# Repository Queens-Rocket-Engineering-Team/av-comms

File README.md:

# Avionics Telemetry (Communications Module, Ground Station, Live Camera etc)
> 2023-2025 Season - Telemetry Projects

-  Repo contains board's **firmware**, **schematics**, and related **documentation and datasheets**.
-  The **Main** branch contains current functional hardware/software
-  **Branches** contain board revisions/versions or planned features/fixes.
-  If you're contributing, **make sure you're working in a branch other than Main**

### Folder Structure
- [`/Schematics`](./Schematics/) : PCB design files (KiCad V8)  
- [`/Firmware`](./Firmware/) : Arduino C/C++ code (for STM32)
- [`/Datasheets`](./Datasheets/) : Datasheets and reference materials

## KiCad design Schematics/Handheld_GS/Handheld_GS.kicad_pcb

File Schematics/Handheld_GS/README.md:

# Portable Ground Station

This directory contains the V1.2 revision of the ground station. It no longer has iss several known problems;

### Updates
- Removed I2C ADC, switched to ESP32-ADCs
- Using direct USB+/- for programming, removed uart bridge
- Added V_BCKP for GPS, (copied circuit from gps antenna board)

### Future Suggestions
- Look into using the MAX17043 for battery management
- Look into using TP4056 for battery charging (cheaper)
- switch to a new battery switch cause it breaks

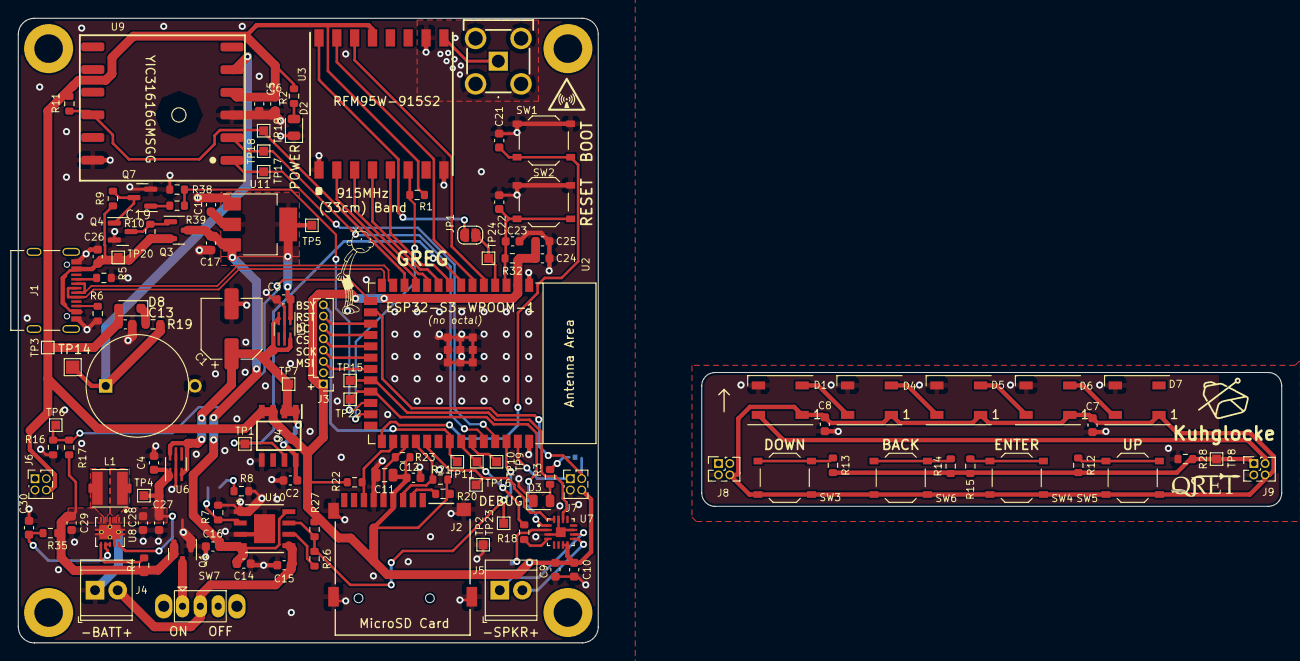
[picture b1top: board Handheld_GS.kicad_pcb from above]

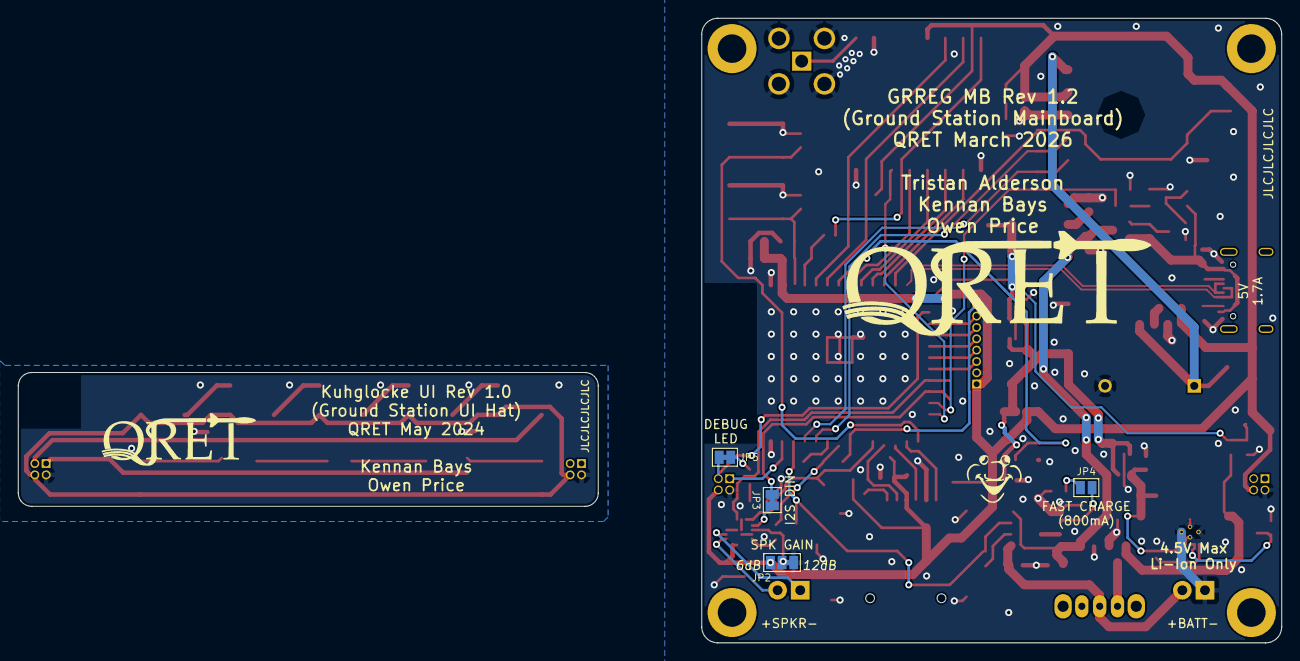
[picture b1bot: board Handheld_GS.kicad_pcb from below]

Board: 2 copper layers, 65.0 x 70.0 mm, 129 parts (4 on the bottom side), 82 nets.

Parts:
AE1: Antenna; PCB114SMAFRAJA
C1: 100uF; CP_Elec_6.3x5.9
C2, C5, C9, C12, C16, C21, C22, C25, C30: 0.1uF; C_0603_1608Metric
C3, C4, C7, C8, C13, C14, C15, C23: 1uF; C_0603_1608Metric
C6: 4.7uF; C_0603_1608Metric
C10, C17, C18, C24, C26, C27, C28, C29: 10uF; C_0603_1608Metric
C11: 47uF; C_0805_2012Metric
C19: 330mF; CB5R5334HF-ZJP
D1, D4, D5, D6, D7: WS2812B; LED_WS2812B_PLCC4_5.0x5.0mm_P3.2mm
D2: INT_PWR_LED (RED); LED_0805_2012Metric
D3: DB_LED (GRN); LED_0805_2012Metric
D8: 1N5819WS; D_SOD-323_HandSoldering
H1, H2, H3, H4: MountingHole; MountingHole_3.2mm_M3_ISO14580_Pad
J1: USB_C_Female_USB2_Small; USB_C_DB-108PWB
J2: MSD-1-A MicroSD Slot; MicroSD_MSD-1-A
J3: PinHeader_1x08_P1.27mm_Vertical
J4: 1S Li-Ion Cell; TerminalBlock_TE_282834-2_1x02_P2.54mm_Horizontal
J5: Speaker; TerminalBlock_TE_282834-2_1x02_P2.54mm_Horizontal
J6: MB_A; PinSocket_2x02_P1.27mm_Vertical
J7: MB_B; PinSocket_2x02_P1.27mm_Vertical
J8: DB_A; HPH2-A-04-UA_PINS
J9: DB_B; HPH2-A-04-UA_PINS
JP1: DIO2_EN; SolderJumper-2_P1.3mm_Open_RoundedPad1.0x1.5mm
JP2: Gain; SolderJumper-3_P1.3mm_Bridged12_Pad1.0x1.5mm_NumberLabels
JP3: SPK_DIN; SolderJumper-2_P1.3mm_Bridged_Pad1.0x1.5mm
JP4: FastCharge; SolderJumper-2_P1.3mm_Open_Pad1.0x1.5mm
JP5: DB_LED_EN; SolderJumper-2_P1.3mm_Bridged_Pad1.0x1.5mm
L1: 2.2uH; L_Taiyo-Yuden_MD-4040
Q1, Q3: AO3401A; SOT-23
Q4, Q7: AO3400A; SOT-23
R1, R3, R11, R16, R20, R21, R22, R23, R26, R27, R32: 10k; R_0603_1608Metric
R2: 1.8k; R_0603_1608Metric
R4, R9, R18, R38: 100k; R_0603_1608Metric
R5, R6: 5.1k; R_0603_1608Metric
R7: 2.4k; R_0603_1608Metric
R8: 3.9k; R_0603_1608Metric
R10: 51k; R_0603_1608Metric
R12, R39: 510; R_0603_1608Metric
R13, R28: 1k; R_0603_1608Metric
R14: 2k; R_0603_1608Metric
R15: 5.6k; R_0603_1608Metric
R17: 20k; R_0603_1608Metric
R19: 100R; R_0603_1608Metric
R35: 100; R_0603_1608Metric
SW1: SW_ESP_BOOT_MODE; SW_Push_1P1T_XKB_TS-1187A
SW2: SW_ESP_RESET; SW_Push_1P1T_XKB_TS-1187A
SW3: SW_DOWN; SW_Push_1P1T_XKB_TS-1187A
SW4: SW_ENTER; SW_Push_1P1T_XKB_TS-1187A
SW5: SW_UP; SW_Push_1P1T_XKB_TS-1187A
SW6: SW_BACK; SW_Push_1P1T_XKB_TS-1187A
SW7: PWR; SS-12D07-VG 4 NS GA PA
TP1: TP_ISENSE; TestPoint_Pad_1.0x1.0mm
TP2: TP_GND; TestPoint_Pad_1.0x1.0mm
TP3: TP_3V3; TestPoint_Pad_1.0x1.0mm
TP4: TP_VPSU; TestPoint_Pad_1.0x1.0mm
TP5: TP_VUSB; TestPoint_Pad_1.0x1.0mm
TP6: B_SENSE; TestPoint_Pad_1.0x1.0mm
TP7: TP_MUX; TestPoint_Pad_1.0x1.0mm
TP8: TP_BTN; TestPoint_Pad_1.0x1.0mm
TP9: IO42; TestPoint_Pad_1.0x1.0mm
TP10: IO41; TestPoint_Pad_1.0x1.0mm
TP11: IO40; TestPoint_Pad_1.0x1.0mm
TP14: BKP; TestPoint_Pad_1.5x1.5mm
TP15: I2S_LRCLK; TestPoint_Pad_1.0x1.0mm
TP16: I2S_BLCK; TestPoint_Pad_1.0x1.0mm
TP17: GPS_RX; TestPoint_Pad_1.0x1.0mm
TP18: GPS_TX; TestPoint_Pad_1.0x1.0mm
TP19: GPS_RST; TestPoint_Pad_1.0x1.0mm
TP20: 5V_RAW; TestPoint_Pad_1.0x1.0mm
TP22: I2S_DIN; TestPoint_Pad_1.0x1.0mm
TP23: CHRG_STAT; TestPoint_Pad_1.0x1.0mm
TP24: IO4; TestPoint_Pad_1.0x1.0mm
U2: ESP32-S3-WROOM-1
U3: RFM95W-915S2; RFM95W
U4: ACS70331EOLC; SOIC127P600X175-8N
U5, U6: LM66100DCKR; SC-70-6_Handsoldering
U7: MAX98357AETE_T; MAX98357_QFN50P300X300X80-17N
U8: TPS63001DRCR; Texas_DRC0010J_ThermalVias
U9: YIC31616GMSGG GPS; YIC31616GMSGG
U10: TPB4056B2X-ES1R; ES1ESOP-8-F_TPK
U11: AMS1117-3.3; SOT-223-3_TabPin2

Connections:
5V_OFF: R38.1, R39.1, U2.24 (GPIO47/SPICLK_P/SUBSPICLK_P_DIFF)
5V_RAW: C26.2, J1.A4 (VBUS), J1.A9 (VBUS), J1.B4 (VBUS), J1.B9 (VBUS), Q3.2 (S), R9.1, R10.1, TP20.1
+3.3V: C5.2, C6.2, C9.1, C10.1, C11.1, C12.1, C13.1, C24.1, C25.1, D8.2 (A), J2.4 (VDD), J3.1 (VCC), J6.4, J7.4, JP2.3 (B), R1.2, R2.2, R11.1, R20.1, R21.1, R22.1, R23.1, R27.2, R32.1, TP3.1, U2.2 (3V3), U3.13 (3.3V), U4.3 (IP-), U4.4 (IP-), U7.7 (VDD), U7.8 (VDD__1), U9.4 (VCC)
+3.3VA: C7.2, C8.2, D1.1 (VDD), D4.1 (VDD), D5.1 (VDD), D6.1 (VDD), D7.1 (VDD), J8.4, J9.4, SW3.1, SW4.1, SW5.1, SW6.1
+5V: C14.1, C16.2, C17.1, Q3.3 (D), U10.4 (VIN), U10.8 (CE), U11.3 (VI)
+BATT: C29.1, Q1.2 (S), R4.1, R17.1, R35.1, U8.5 (VIN)
/GPS_BCKP: C19.1, R19.2, TP14.1, U9.5 (V_BCKP)
/LA: L1.2, U8.2 (L2)
/LB: L1.1, U8.4 (L1)
ARGB_DATA: J7.3, JP5.1 (A), U2.16 (GPIO46)
ARGB_DATA_DB: D1.4 (DIN), J9.3
BATT_SENSE: R16.1, R17.2, TP6.1, U2.15 (GPIO3/TOUCH3/ADC1_CH2)
BUTTONS: J7.1, U2.39 (GPIO1/TOUCH1/ADC1_CH0)
BUTTONS_DB: J9.1, R12.2, R13.2, R14.1, R15.2, R28.2, TP8.1
CHRG_STAT: R26.2, R27.1, TP23.1, U2.38 (GPIO2/TOUCH2/ADC1_CH1), U10.7 (CHRG)
CLK_SDMMC: J2.5 (CLK), R23.2, U2.29 (SPIIO7/GPIO36/FSPICLK/SUBSPICLK)
CMD_SDMMC: J2.3 (CMD), R21.2, U2.30 (SPIDQS/GPIO37/FSPIQ/SUBSPIQ)
CS_EINK: J3.5 (CS), U2.19 (GPIO11/TOUCH11/ADC2_CH0/FSPID/FSPIIO5/S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)
CS_RF: U2.8 (GPIO15/U0RTS/ADC2_CH4/XTAL_32K_P), U3.5 (NSS)
CURR_SENSE: TP1.1, U2.7 (GPIO7/TOUCH7/ADC1_CH6), U4.7 (VOUT)
D0_SDMMC: J2.7 (DAT0), R22.2, U2.28 (SPIIO6/GPIO35/FSPID/SUBSPID)
DIO0_RF: U2.5 (GPIO5/TOUCH5/ADC1_CH4), U3.14 (DIO0)
DIO1_RF: U2.6 (GPIO6/TOUCH6/ADC1_CH5), U3.15 (DIO1)
DIO2_RF: JP1.2 (B), TP24.1, U2.4 (GPIO4/TOUCH4/ADC1_CH3)
EINK_BUSY: J3.8 (BUSY), TP11.1, U2.33 (MTDO/GPIO40/CLK_OUT2)
EINK_DC: J3.6 (DC), U2.18 (GPIO10/TOUCH10/ADC1_CH9/FSPICS0/FSPIIO4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)
ESP32_EN: C22.2, C23.2, R32.2, SW2.2, U2.3 (EN)
GND: AE1.2 (Shield), C1.2, C2.2, C3.2, C4.2, C5.1, C6.1, C9.2, C10.2, C11.2, C12.2, C13.2, C14.2, C15.1, C16.1, C17.2, C18.2, C19.2, C21.1, C22.1, C23.1, C24.2, C25.2, C26.1, C27.2, C28.2, C29.2, C30.2, D2.1 (K), D3.1 (K), J1.A1 (GND), J1.A12 (GND), J1.B1 (GND), J1.B12 (GND), J2.6 (VSS), J2.10 (SHIELD), J3.2 (GND), J4.1, J6.2, J7.2, JP2.1 (A), Q1.1 (G), Q4.2 (S), Q7.2 (S), R5.2, R6.2, R7.1, R8.2, R16.2, R38.2, SW1.1, SW2.1, TP2.1, U2.1 (GND), U2.40 (GND), U2.41 (GND), U3.1 (GND), U3.8 (GND), U3.10 (GND), U4.5 (GND), U5.2 (GND), U5.5 (ST), U6.2 (GND), U6.5 (ST), U7.3 (GND), U7.11 (GND__1), U7.15 (GND__2), U7.17 (EP), U8.3 (PGND), U8.9 (GND), U8.11 (PGND), U9.3 (GND), U9.12 (GND), U10.1 (TEMP), U10.3 (GND), U10.9 (GND), U11.1 (GND)
GND2: C7.1, C8.1, D1.3 (VSS), D4.3 (VSS), D5.3 (VSS), D6.3 (VSS), D7.3 (VSS), J8.2, J9.2, R28.1
GPIO0: C21.2, SW1.2, U2.27 (GPIO0/BOOT)
GPS_RST: R11.2, TP19.1, U2.12 (GPIO8/TOUCH8/ADC1_CH7/SUBSPICS1), U9.10 (RESET)
I2S_BCLK_SPK: TP16.1, U2.31 (GPIO38/FSPIWP/SUBSPIWP), U7.16 (BCLK)
I2S_DIN_SPK: JP3.2 (B), TP22.1, U2.23 (GPIO21)
I2S_LRCLK_SPK: TP15.1, U2.22 (GPIO14/TOUCH14/ADC2_CH3/FSPIWP/FSPIDQS/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), U7.14 (LRCLK)
MISO_EINK: TP9.1, U2.35 (MTMS/GPIO42)
MISO_RF: U2.11 (GPIO18/U1RXD/ADC2_CH7/CLK_OUT3), U3.2 (MISO)
MOSI_EINK: J3.3 (DIN), U2.21 (GPIO13/TOUCH13/ADC2_CH2/FSPIQ/FSPIIO7/S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)
MOSI_RF: U2.10 (GPIO17/U1TXD/ADC2_CH6), U3.3 (MOSI)
unnamed: AE1.1 (A), U3.9 (ANT)
unnamed: D1.2 (DOUT), D4.4 (DIN)
unnamed: D2.2 (A), R2.1
unnamed: D3.2 (A), R3.1
unnamed: D4.2 (DOUT), D5.4 (DIN)
unnamed: D5.2 (DOUT), D6.4 (DIN)
unnamed: D6.2 (DOUT), D7.4 (DIN)
unnamed: D8.1 (K), R19.1
unnamed: J1.A5 (CC1), R5.1
unnamed: J1.B5 (CC2), R6.1
unnamed: J2.2 (DAT3/CD), R20.2
unnamed: J5.1, U7.10 (OUTN)
unnamed: J5.2, U7.9 (OUTP)
unnamed: JP1.1 (A), U3.16 (DIO2)
unnamed: JP2.2 (C), U7.2 (GAIN_SLOT)
unnamed: JP3.1 (A), U7.1 (DIN)
unnamed: JP4.1 (A), R8.1
unnamed: JP4.2 (B), R7.2, U10.2 (PROG)
unnamed: JP5.2 (B), R3.2
unnamed: Q1.3 (D), SW7.1 (A)
unnamed: Q3.1 (G), Q4.3 (D), R10.2
unnamed: Q4.1 (G), Q7.3 (D), R9.2
unnamed: Q7.1 (G), R39.2
unnamed: R12.1, SW5.2
unnamed: R13.1, SW3.2
unnamed: R14.2, SW6.2
unnamed: R15.1, SW4.2
unnamed: R18.2, U7.4 (SD_MODE)
unnamed: R4.2, U8.6 (EN)
unnamed: C30.1, R35.2, U8.7 (PS/SYNC), U8.8 (VINA)
unnamed: R26.1, U10.6 (STBY)
RAW_BATT: C15.2, J4.2, SW7.2 (B), U10.5 (BAT)
RESET_EINK: J3.7 (RST), U2.17 (GPIO9/TOUCH9/ADC1_CH8/FSPIHD/SUBSPIHD)
RESET_RF: R1.1, U2.25 (GPIO48/SPICLK_N/SUBSPICLK_N_DIFF), U3.6 (RESET)
SCK_EINK: J3.4 (CLK), U2.20 (GPIO12/TOUCH12/ADC2_CH1/FSPICLK/FSPIIO6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)
SCK_RF: U2.9 (GPIO16/U0CTS/ADC2_CH5/XTAL_32K_N), U3.4 (SCK)
SPK_ON: R18.1, TP10.1, U2.34 (MTDI/GPIO41/CLK_OUT1)
UART1_GPS_RX: TP18.1, U2.36 (U0RXD/GPIO44/CLK_OUT2), U9.2 (TXD)
UART1_GPS_TX: TP17.1, U2.37 (U0TXD/GPIO43/CLK_OUT1), U9.1 (RXD)
USB_D+: J1.A6 (D+), J1.B6 (D+), U2.14 (GPIO20/U1CTS/ADC2_CH9/CLK_OUT1/USB_D+)
USB_D-: J1.A7 (D-), J1.B7 (D-), U2.13 (GPIO19/U1RTS/ADC2_CH8/CLK_OUT2/USB_D-)
V_MUX: C1.1, C2.1, TP7.1, U4.1 (IP+), U4.2 (IP+), U4.8 (VCC), U5.3 (*CE), U5.6 (VOUT), U6.3 (*CE), U6.6 (VOUT)
V_PSU: C4.1, C27.1, C28.1, TP4.1, U6.1 (VIN), U8.1 (VOUT), U8.10 (FB)
V_REGUSB: C3.1, C18.1, TP5.1, U5.1 (VIN), U11.2 (VO)

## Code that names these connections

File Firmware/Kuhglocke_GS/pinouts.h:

#pragma once

/*
 * Pin definitions for the Kuhglocke ground station (Rev 1.0)
 */

#define GPS_TX_PIN 20
#define GPS_RX_PIN 19
#define GPS_RESET_PIN 8

#define MENU_BTNS_PIN 1
#define ARGB_DATA_PIN 46
#define DB_LED_PIN ARGB_DATA_PIN //same pin as RGB

#define CHRG_STAT_PIN 2
#define DISABLE_5V_PIN 3

#define RF_DIO2_PIN 4
#define RF_DIO0_PIN 5
#define RF_DIO1_PIN 6
#define RF_RESET_PIN 7
#define RF_MOSI_PIN 17
#define RF_MISO_PIN 18
#define RF_CS_PIN 15
#define RF_SCK_PIN 16

#define EINK_RESET_PIN 9
#define EINK_DC_PIN 10
#define EINK_CS_PIN 11
#define EINK_SCK_PIN 12
#define EINK_MOSI_PIN 13
#define EINK_MISO_PIN 42
#define EINK_BUSY_PIN 40

#define SPK_I2S_LRCLK_PIN 14
#define SPK_I2S_DIN_PIN 21
#define SPK_I2S_BCLK_PIN 38
#define SPK_ON_PIN 41

#define SDMMC_CMD_PIN 35
#define SDMMC_CLK_PIN 36
#define SDMMC_D0_PIN 37

#define I2C_SCL_PIN 47
#define I2C_SDA_PIN 48
#define NAU7802_ADDR 0x2A
#define P3T1755_ADDR 0x48

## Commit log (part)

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2026-01-22 Split Kuhglocke_GS into modules (GPS/global/radio/screen/sensors/UI)
2026-01-31 init commit for migrating avionics comms devices to dedicated repo - updated datasheets links to local file - missing exact LoRaSX162 datasheet
2026-02-04 more optimized
2026-03-25 start of new migrated ground station project
2026-03-28 Updated ground station with suggest changes and more, routing done
2026-03-30 Update Silkscreen and Added some 3D models
2026-03-31 added silkscreen for eink pins
2026-04-01 update datasheet referencing
2026-04-01 add live camera hardware and firmware
2026-04-01 update READMEs
2026-05-01 add 3d models to all parts
2026-05-13 All work during exam season
    (not sure why there are so many extra files)
2026-06-12 remove build artifacts
2026-06-12 move old kuhglocke firmware to support aim integration
2026-06-12 remove stale submodule
2026-06-12 fix gitignore
2026-06-14 feat(comms): integrate dynamic state reporting and low-power event subscription
2026-06-15 av-telemetry: migrate Communications_Module to node.* convention (schema v2)
    Thin main.cpp + node.{cpp,h}; build against schema-v2 av-libraries;
    platformio and README updates.
2026-06-16 Phase 1: Migrate Kuhglocke GS to PlatformIO and fix radio-SPI bug
2026-06-16 Phase 2: Perform subtract-first cleanup and encapsulate state modules
2026-06-16 Phase 3: Integrate aim_catalog.h LoRa decode and forward aim::Msg framed records
2026-06-16 Phase 3.5: Commit scaling correctness fixes from working tree
2026-06-16 Kuhglocke_GS: Phase 4 — Retire web server and integrate QLCP uplink
2026-06-16 Kuhglocke_GS: Perform subtract-first code cleanups and documentation
2026-06-18 Communications: pass nowMs into service()
    Match the updated AimNetwork::service(nowMs, state, errorBits) signature.
2026-06-21 Communications: trim self-tracking from liveness, clean up node layout
    Comms no longer tracks itself in the liveness table (kTrackedNodes 6→5).
    Reorder functions to match node convention, apply naming cleanup, and
    tighten console hook registration.
2026-06-25 feature: create a shared library for LoRa comms decoding and health checking
2026-06-26 feature: Integrate new lora link layer, add new menu pages: node healths, rf tuning
